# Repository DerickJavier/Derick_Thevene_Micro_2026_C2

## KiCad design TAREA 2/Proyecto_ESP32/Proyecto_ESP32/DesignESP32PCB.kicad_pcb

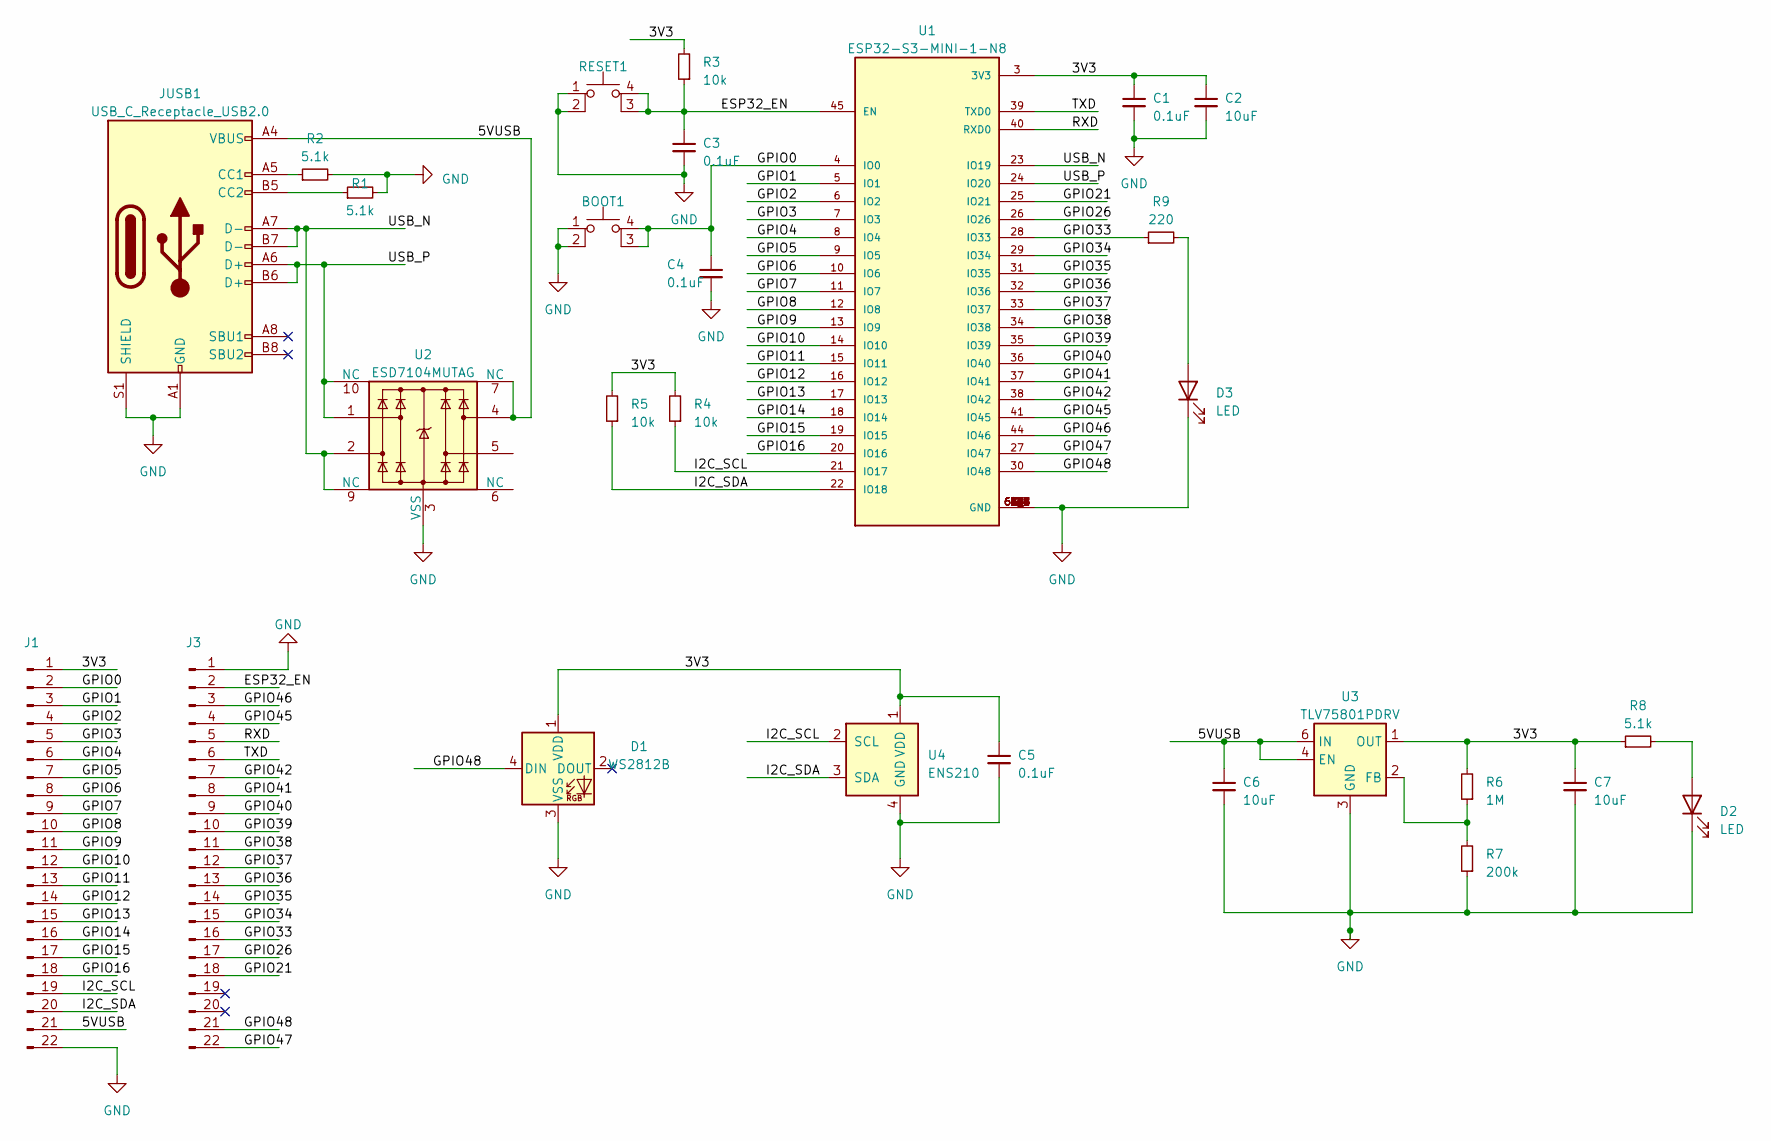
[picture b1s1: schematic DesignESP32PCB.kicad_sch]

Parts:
BOOT1: SW_SPST_PTS810
C1, C3, C4, C5: 0.1uF; C_0603_1608Metric
C2, C6, C7: 10uF; C_0603_1608Metric
D1: WS2812B; LED_WS2812B_PLCC4_5.0x5.0mm_P3.2mm
D2: LED; LED_0603_1608Metric
D3: LED; LED_D3.0mm
J1, J3: PinHeader_1x22_P2.54mm_Vertical
JUSB1: USB_C_Receptacle_USB2.0; USB_C_Receptacle_GCT_USB4105-xx-A_16P_TopMnt_Horizontal
R1, R2, R8: 5.1k; R_0603_1608Metric
R3, R4, R5: 10k; R_0603_1608Metric
R6: 1M; R_0603_1608Metric
R7: 200k; R_0603_1608Metric
R9: 220; R_0603_1608Metric
RESET1: SW_SPST_PTS810
U1: ESP32-S3-MINI-1-N8; XCVR_ESP32-S3-MINI-1-N8; PARTREV v0.6
U2: ESD7104MUTAG; Diodes_UDFN-10_1.0x2.5mm_P0.5mm
U3: TLV75801PDRV; WSON-6-1EP_2x2mm_P0.65mm_EP1x1.6mm
U4: ENS210; AMS_QFN-4-1EP_2x2mm_P0.95mm_EP0.7x1.6mm

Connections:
/3V3: C1.1, C2.1, C5.1, C7.1, D1.1 (VDD), J1.1, R3.2, R4.2, R5.2, R6.2, R8.1, U1.3 (3V3), U3.1 (OUT), U4.1 (VDD)
/5VUSB: C6.1, J1.21, JUSB1.A4 (VBUS), JUSB1.A9 (VBUS), JUSB1.B4 (VBUS), JUSB1.B9 (VBUS), U2.4, U2.7 (NC), U3.4 (EN), U3.6 (IN)
/ESP32_EN: C3.1, J3.2, R3.1, RESET1.3 (K), RESET1.4 (A), U1.45 (EN)
/GPIO0: BOOT1.3 (K), BOOT1.4 (A), C4.1, J1.2, U1.4 (IO0)
/GPIO1: J1.3, U1.5 (IO1)
/GPIO2: J1.4, U1.6 (IO2)
/GPIO3: J1.5, U1.7 (IO3)
/GPIO4: J1.6, U1.8 (IO4)
/GPIO5: J1.7, U1.9 (IO5)
/GPIO6: J1.8, U1.10 (IO6)
/GPIO7: J1.9, U1.11 (IO7)
/GPIO8: J1.10, U1.12 (IO8)
/GPIO9: J1.11, U1.13 (IO9)
/GPIO10: J1.12, U1.14 (IO10)
/GPIO11: J1.13, U1.15 (IO11)
/GPIO12: J1.14, U1.16 (IO12)
/GPIO13: J1.15, U1.17 (IO13)
/GPIO14: J1.16, U1.18 (IO14)
/GPIO15: J1.17, U1.19 (IO15)
/GPIO16: J1.18, U1.20 (IO16)
/GPIO21: J3.18, U1.25 (IO21)
/GPIO26: J3.17, U1.26 (IO26)
/GPIO33: J3.16, R9.1, U1.28 (IO33)
/GPIO34: J3.15, U1.29 (IO34)
/GPIO35: J3.14, U1.31 (IO35)
/GPIO36: J3.13, U1.32 (IO36)
/GPIO37: J3.12, U1.33 (IO37)
/GPIO38: J3.11, U1.34 (IO38)
/GPIO39: J3.10, U1.35 (IO39)
/GPIO40: J3.9, U1.36 (IO40)
/GPIO41: J3.8, U1.37 (IO41)
/GPIO42: J3.7, U1.38 (IO42)
/GPIO45: J3.4, U1.41 (IO45)
/GPIO46: J3.3, U1.44 (IO46)
/GPIO47: J3.22, U1.27 (IO47)
/GPIO48: D1.4 (DIN), J3.21, U1.30 (IO48)
/I2C_SCL: J1.19, R4.1, U1.21 (IO17), U4.2 (SCL)
/I2C_SDA: J1.20, R5.1, U1.22 (IO18), U4.3 (SDA)
/RXD: J3.5, U1.40 (RXD0)
/TXD: J3.6, U1.39 (TXD0)
/USB_N: JUSB1.A7 (D-), JUSB1.B7 (D-), U1.23 (IO19), U2.2, U2.9 (NC)
/USB_P: JUSB1.A6 (D+), JUSB1.B6 (D+), U1.24 (IO20), U2.1, U2.10 (NC)
GND: BOOT1.1, BOOT1.2, C1.2, C2.2, C3.2, C4.2, C5.2, C6.2, C7.2, D1.3 (VSS), D2.1 (K), D3.1 (K), J1.22, J3.1, JUSB1.A1 (GND), JUSB1.A12 (GND), JUSB1.B1 (GND), JUSB1.B12 (GND), JUSB1.S1 (SHIELD), R1.2, R2.2, R7.1, RESET1.1, RESET1.2, U1.1 (GND), U1.2 (GND), U1.42 (GND), U1.43 (GND), U1.46 (GND), U1.47 (GND), U1.48 (GND), U1.49 (GND), U1.50 (GND), U1.51 (GND), U1.52 (GND), U1.53 (GND), U1.54 (GND), U1.55 (GND), U1.56 (GND), U1.57 (GND), U1.58 (GND), U1.59 (GND), U1.60 (GND), U1.61 (GND), U1.61_1 (GND), U1.61_2 (GND), U1.61_3 (GND), U1.61_4 (GND), U1.61_5 (GND), U1.61_6 (GND), U1.61_7 (GND), U1.61_8 (GND), U1.62 (GND), U1.63 (GND), U1.64 (GND), U1.65 (GND), U2.3 (VSS), U2.8 (VSS), U3.3 (GND), U3.7 (GND), U4.4 (GND), U4.5 (GND)
unnamed: D2.2 (A), R8.2
unnamed: D3.2 (A), R9.2
unnamed: JUSB1.A5 (CC1), R2.1
unnamed: JUSB1.B5 (CC2), R1.1
unnamed: R6.1, R7.2, U3.2 (FB)

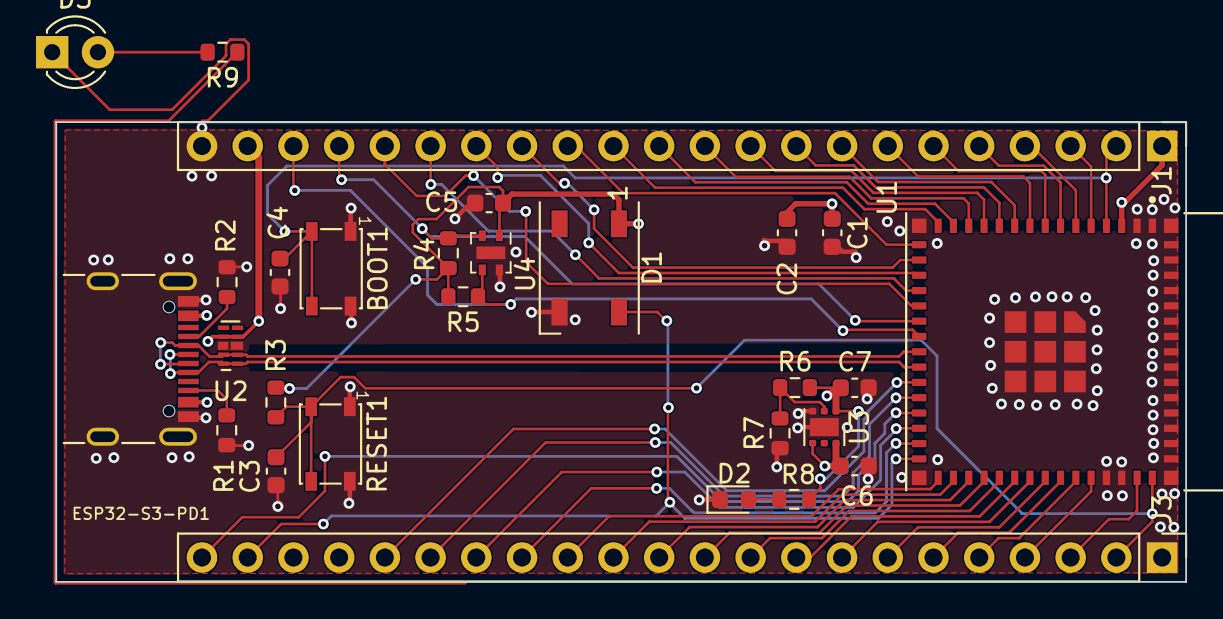
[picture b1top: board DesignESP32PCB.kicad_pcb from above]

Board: 4 copper layers, 62.8 x 25.5 mm, 28 parts (0 on the bottom side), 48 nets.

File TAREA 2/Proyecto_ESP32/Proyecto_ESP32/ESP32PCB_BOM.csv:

Reference,Qty,Part#,Value,Footprint
U1,1,ESP32-S3-MINI-1-N8,-,ESP32-S3-MINI-1-N8:XCVR_ESP32-S3-MINI-1-N8
U2,1,ESD7104MUTAG,-,Package_DFN_QFN:Diodes_UDFN-10_1.0x2.5mm_P0.5mm
U3,1,TLV75801PDRVR,-,Package_SON:WSON-6-1EP_2x2mm_P0.65mm_EP1x1.6mm
U4,1,ENS210-LQFM,-,Package_DFN_QFN:AMS_QFN-4-1EP_2x2mm_P0.95mm_EP0.7x1.6mm
"BOOT1, RESET1",2,PTS810 SJK 250 SMTR LFS,-,Button_Switch_SMD:SW_SPST_PTS810
JUSB1,1,USB4105-GF-A,-,Connector_USB:USB_C_Receptacle_GCT_USB4105-xx-A_16P_TopMnt_Horizontal
D1,1, COM-16347,-,LED_SMD:LED_WS2812B_PLCC4_5.0x5.0mm_P3.2mm
D2,1,150060RS75000,-,LED_SMD:LED_0603_1608Metric
"J1, J3",2,61302211121,-,Connector_PinHeader_2.54mm:PinHeader_1x22_P2.54mm_Vertical
"C1, C3, C4, C5",4,CC0603KRX7R7BB104,0.1uF,Capacitor_SMD:C_0603_1608Metric
"C2, C6, C7",3,CL10A106MQ8NNNC,10uF,Capacitor_SMD:C_0603_1608Metric
"R1, R2, R8",3,RC0603FR-075K1L,5.1k,Resistor_SMD:R_0603_1608Metric
"R3, R4, R5",3,RC0603FR-0710KL,10k,Resistor_SMD:R_0603_1608Metric
R6,1,RT0603BRD071ML,1M,Resistor_SMD:R_0603_1608Metric
R7,1,RC0603FR-07200KL,200k,Resistor_SMD:R_0603_1608Metric

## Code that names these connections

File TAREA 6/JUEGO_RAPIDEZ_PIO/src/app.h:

#ifndef APP_H
#define APP_H

#include <stdint.h>
#include <stdbool.h>

#ifdef __cplusplus
extern "C" {
#endif

/* ===== Pines ===== */
#define BTN1_PIN 4   /* GPIO4  = Boton 1 (activo LOW, pull-up) */
#define BTN2_PIN 13  /* GPIO13 = Boton 2 (activo LOW, pull-up) */
#define LED1_PIN 2   /* GPIO2  = LED integrado / LED 1         */
#define LED2_PIN 15  /* GPIO15 = LED 2                          */

/* ===== Capa de hardware (implementada en puente_arduino.cpp) ===== */
void     hal_configurar_pines(void);
uint32_t hal_micros(void);
void     hal_esperar_ms(uint32_t ms);
uint32_t hal_aleatorio(uint32_t minimo, uint32_t maximo);
bool     hal_leer_boton(uint8_t pin);            /* true si esta presionado */
void     hal_escribir_led(uint8_t pin, bool encendido);
void     hal_log(const char *texto);
void     hal_log_formato(const char *formato, ...);

/* ===== Capa de red WiFi + MQTT (implementada en puente_arduino.cpp) ===== */
void net_iniciar(void);
bool net_conectado(void);
void net_procesar(void);
void net_reconectar(void);
bool net_publicar(const char *topico, const char *mensaje);

/* ===== Logica del juego (implementada en main.c) ===== */
void juego_iniciar(void);
void juego_iterar(void);

#ifdef __cplusplus
}
#endif

#endif /* APP_H */

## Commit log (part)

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2026-06-12 Add files via upload
    Resumen de los capitulos 4 y 5 del libro matematica computacional
